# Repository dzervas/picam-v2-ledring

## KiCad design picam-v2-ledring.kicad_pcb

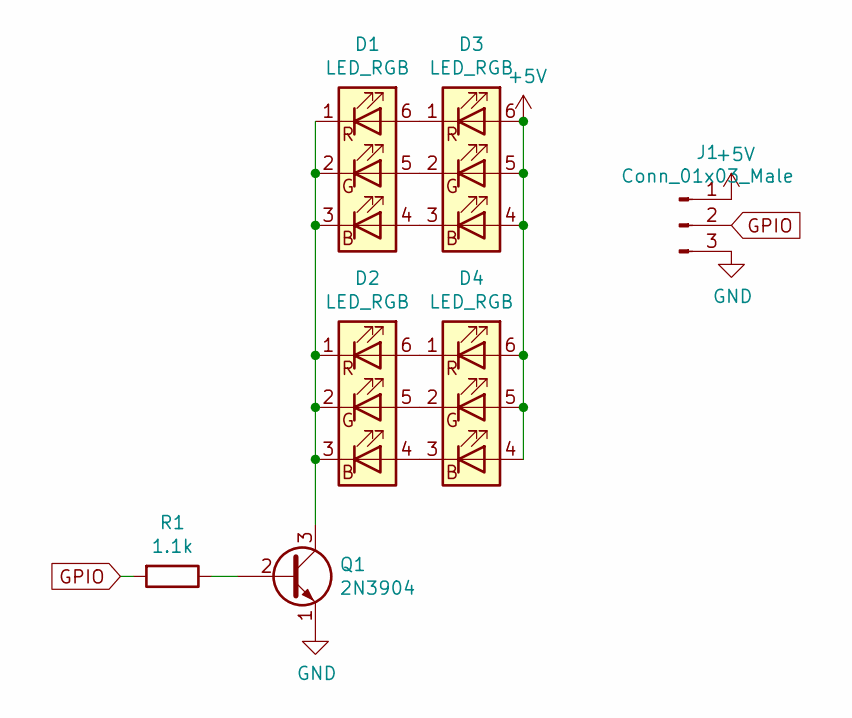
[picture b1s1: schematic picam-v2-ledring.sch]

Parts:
D1, D2, D3, D4: LED_RGB; LED_RGB_5050-6
J1: Conn_01x03_Male; PinHeader_1x03_P2.54mm_Vertical
Q1: 2N3904; TO-92_Inline
R1: 1.1k; R_0805_2012Metric_Pad1.20x1.40mm_HandSolder

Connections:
+5V: D3.4 (BA), D3.5 (GA), D3.6 (RA), D4.4 (BA), D4.5 (GA), D4.6 (RA), J1.1
GND: J1.3, Q1.1 (E)
GPIO: J1.2, R1.2
unnamed: D1.1 (RK), D1.2 (GK), D1.3 (BK), D2.1 (RK), D2.2 (GK), D2.3 (BK), Q1.3 (C)
unnamed: D1.4 (BA), D3.3 (BK)
unnamed: D1.5 (GA), D3.2 (GK)
unnamed: D1.6 (RA), D3.1 (RK)
unnamed: D2.4 (BA), D4.3 (BK)
unnamed: D2.5 (GA), D4.2 (GK)
unnamed: D2.6 (RA), D4.1 (RK)
unnamed: Q1.2 (B), R1.1

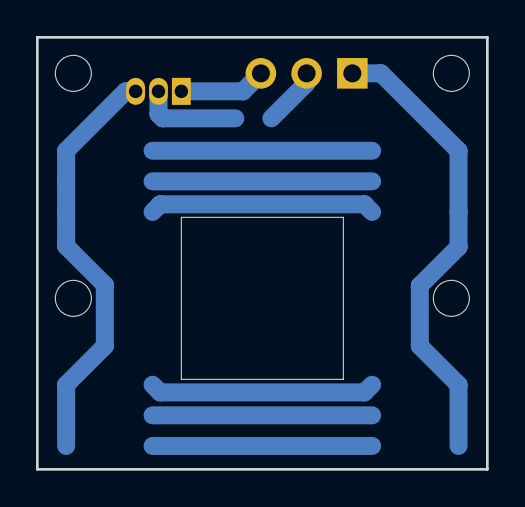
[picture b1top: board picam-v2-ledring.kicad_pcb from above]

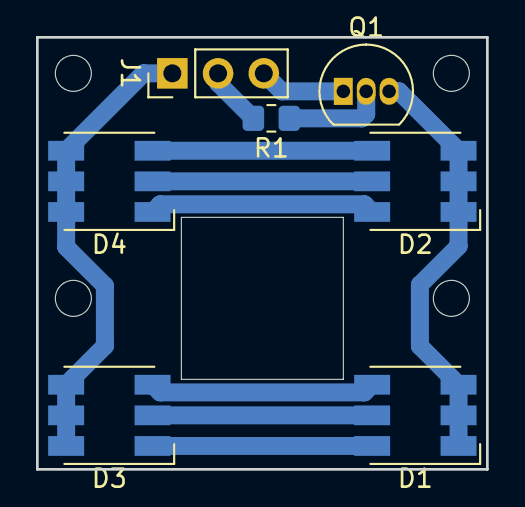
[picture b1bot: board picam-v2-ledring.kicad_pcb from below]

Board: 2 copper layers, 25.0 x 24.0 mm, 7 parts (7 on the bottom side), 11 nets.
